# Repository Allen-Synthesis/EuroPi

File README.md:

# EuroPi
The EuroPi is a user reprogrammable [Eurorack](https://en.wikipedia.org/wiki/Eurorack) module developed by [Allen Synthesis](https://allensynthesis.co.uk) that uses the [Raspberry Pi Pico](https://www.raspberrypi.com/products/raspberry-pi-pico/) to process and produce modular level signals based on code written in [MicroPython](https://micropython.org/). The entire project is open-source.

## Documentation
### Hardware
The hardware source files and documentation (including build guides) can be found in the [hardware overview](hardware/README.md), and kits can be bought directly from [Allen Synthesis](https://allensynthesis.square.site/product/europi-panel-pcb/16?cp=true&sa=true&sbp=false&q=false).

### Software
Before using any of the software, follow the [programming_instructions](software/programming_instructions.md) to set up and calibrate your module.
A list of user contributed scripts (along with descriptions for their usage) can be found in [contrib/README.md](software/contrib/README.md).

The EuroPi firmware allows you to interact with the hardware easily using code written in MicroPython. You can read the full list of available functions in the [EuroPi API Documentation](https://allen-synthesis.github.io/EuroPi/), which also includes some examples of some of those functions can be used. Some of the less obvious but potentially useful functions are also explained in more depth in [interesting_things.md](software/interesting_things.md).

If you would like to extend any of the features of the EuroPi software, you can view the [firmware source code](software/firmware/europi.py), and make contributions of your own after reading the [contribution guidelines](contributing.md).

### Issues
If you find any bugs, either in the software, the hardware, or the documentation, please [create a GitHub issue](https://github.com/Allen-Synthesis/EuroPi/issues/new/choose) so it can be fixed by one of the maintainers. There are issue templates available, so please choose whichever is most relevant.

### AI Policy 
This is a project that is both explicitly aware of, and reliant on, its social context; the module's licenses are deliberately 'free' and open-source, and that fact is what has allowed its community to develop itself, and consequently develop the EuroPi module.
To paraphrase [Dan McQuillan](https://www.youtube.com/watch?v=mh0U2o5Ysms), "AI removes the cultural context that underpins our social relations" - A tool which produces an output without regard for social context cannot be used to meaningfully contribute to any project that specifically aims to analyse and engage with that context.

We are not able to know with certainty that any contribution is AI-free, however any pull requests which have clearly relied on it will be rejected. For the reasons described above we hope that you will choose to develop without it, not just to ensure a quick merge, but for the benefit of the open-source community and society as a whole.
All of the core components of the EuroPi (the firmware and hardware) are entirely AI-free.

## Specification
* 6 0-10V Control Voltage outputs, each with indicator LED
* 2 Knobs with 12 bit resolution
* 2 Push Buttons
* 1 0-12V Control Voltage input with 12 bit resolution
* 1 Digital input for external clocking or gate sources
* 128x32 OLED Display
* I²C expansion header on the rear for extra sensors or outputs

## License
This module, and any documentation included in this repository, is entirely "free" software and hardware. The hardware is [certified by the Open Source Hardware Association](https://certification.oshwa.org/uk000048.html)

* Software: [Apache 2.0](software/LICENSE)
* Hardware: [CERN OHL-S v2](hardware/LICENSE)
* Documentation: [CC0 1.0](LICENSE)

Anyone is welcome to design their own versions of the idea, or modify my designs.
The only thing I would ask is that you refrain from using the brand name 'Allen Synthesis' on your DIY builds if they have modified my files in any way, just to prevent any confusion if they end up being re-sold or distributed. This is in line with section 8.2 of the CERN license. You may use the brand name if you have simply copied the files from this repository to replicate without modification.

If you have a bug fix or improvement that you think is worth sharing, then feel free to send over any pictures or documentation and it can be merged with the main project!

## Disclaimer
Recreate any of the files found in this repository at your own risk; I will attempt to solve any issues that you might have with my designs, but I can't guarantee that there are not minor bugs in any of the documents, both hardware and software. If you want a module or kit that you know will work and will have customer support, you can order one directly from [Allen Synthesis](https://allensynthesis.co.uk/).

**NOTE:** This repository relates to the EuroPi module, however some users may be expecting to see what is now referred to as the 'EuroPi Prototype'. The repository for this (now deprecated) module [can be found here](https://github.com/roryjamesallen/EuroPi-Prototype)

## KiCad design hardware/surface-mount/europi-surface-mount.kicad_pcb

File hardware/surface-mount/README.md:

# EuroPi (surface-mount)

This is a version of the EuroPi that has all of the components other than the Pico, power header, and panel components pre-soldered using SMD packages. This makes for a much simpler DIY build, as well as a thinner end result. It has identical technical specifications to the through-hole version and adds the hardware required for input detection.

The board files for this version are designed in [KiCad](https://www.kicad.org/) so are a more friendly starting point for third-party development or modification.

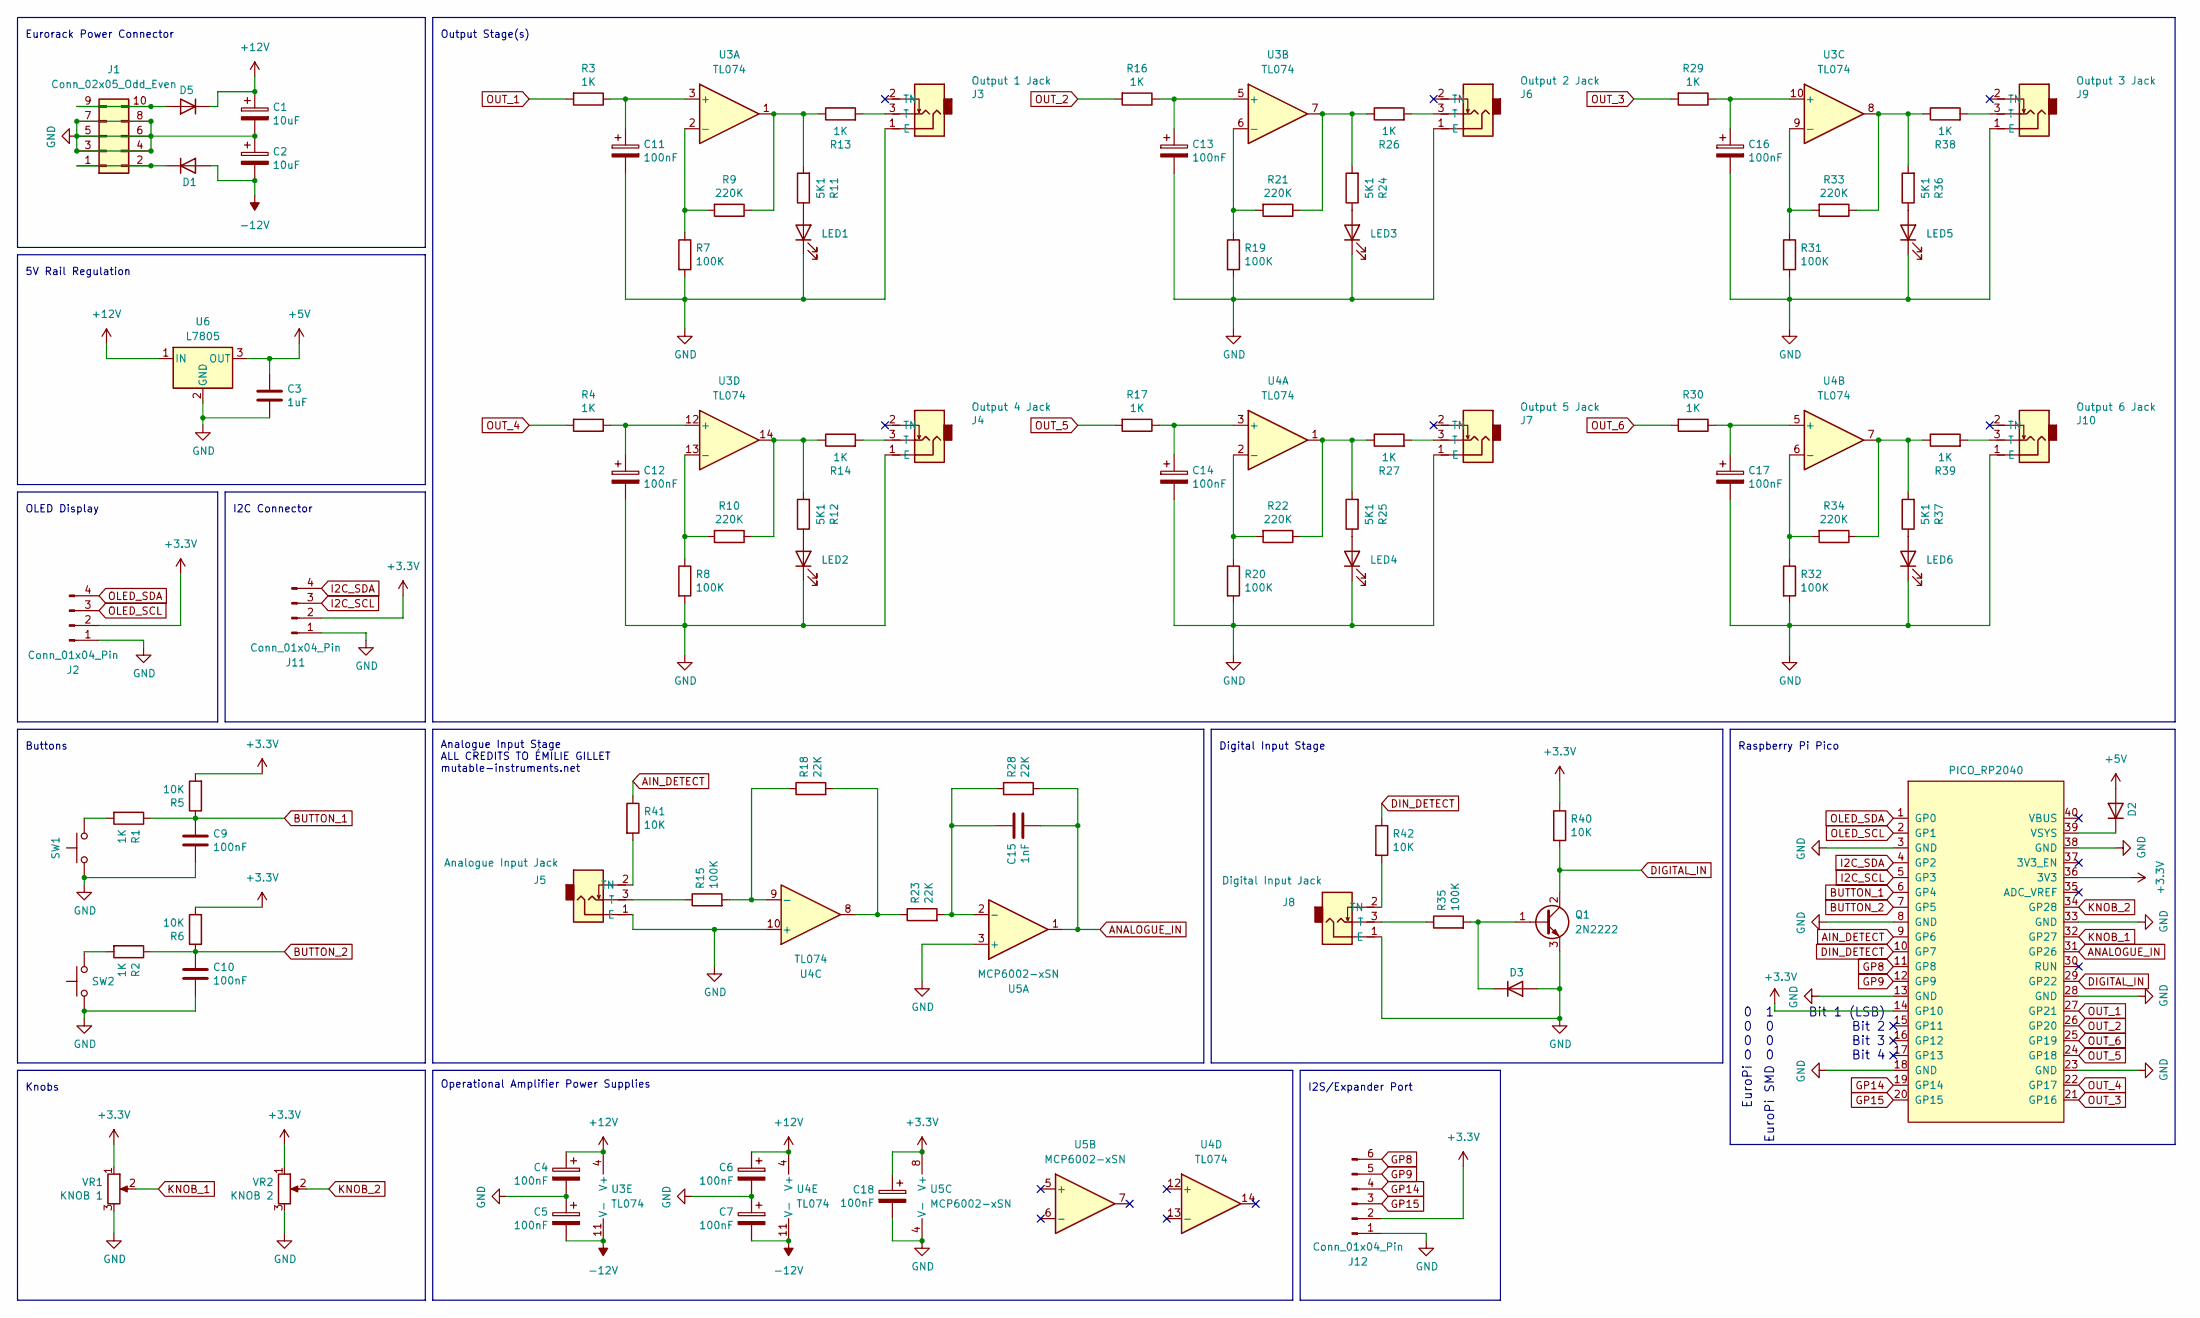
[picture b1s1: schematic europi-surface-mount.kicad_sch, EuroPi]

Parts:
C1, C2: 10uF; C_0805_2012Metric
C3: 1uF; C_0603_1608Metric
C4, C5, C6, C7, C9, C10, C11, C12, C13, C14, C16, C17, C18: 100nF; C_0603_1608Metric
C15: 1nF; C_0603_1608Metric
D1, D2, D5: D; D_SMA; LCSC Part C5356810
D3: D; D_SMA; LCSC Part C5148475
J1: Conn_02x05_Odd_Even; power-header-10-pin-unlabelled
J2: Conn_01x04_Pin; PinHeader_1x04_P2.54mm_Vertical
J3: Output 1 Jack; jack-thonkiconn-mono
J4: Output 4 Jack; jack-thonkiconn-mono
J5: Analogue Input Jack; jack-thonkiconn-mono
J6: Output 2 Jack; jack-thonkiconn-mono
J7: Output 5 Jack; jack-thonkiconn-mono
J8: Digital Input Jack; jack-thonkiconn-mono
J9: Output 3 Jack; jack-thonkiconn-mono
J10: Output 6 Jack; jack-thonkiconn-mono
J11: Conn_01x04_Pin; JST_PH_B4B-PH-K_1x04_P2.00mm_Vertical
J12: Conn_01x04_Pin; JST_PH_B6B-PH-K_1x06_P2.00mm_Vertical
LED1, LED2, LED3, LED4, LED5, LED6: LED; led-3mm
Q1: 2N2222; SOT-89-3; LCSC Part C21714170
R1, R2, R3, R4, R13, R14, R16, R17, R26, R27, R29, R30, R38, R39: 1K; R_0603_1608Metric
R5, R6, R40, R41, R42: 10K; R_0603_1608Metric
R7, R8, R15, R19, R20, R31, R32, R35: 100K; R_0603_1608Metric
R9, R10, R21, R22, R33, R34: 220K; R_0603_1608Metric
R11, R12, R24, R25, R36, R37: 5K1; R_0603_1608Metric
R18, R23, R28: 22K; R_0603_1608Metric
SW1, SW2: SW_Push; switch-momentary-c&k
U2: PICO_RP2040; raspberry-pi-pico
U3, U4: TL074; SOIC-14_3.9x8.7mm_P1.27mm; LCSC Part C6963
U5: MCP6002-xSN; SOIC-8_3.9x4.9mm_P1.27mm; LCSC Part C7377
U6: L7805; TO-252-2; LCSC Part C7394043
VR1: KNOB 1; potentiometer-9mm
VR2: KNOB 2; potentiometer-9mm

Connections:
+3.3V: C18.1, J2.2, J11.2, J12.2, R5.2, R6.2, R40.1, U2.14 (GP10), U2.36 (3V3), U5.8 (V+), VR1.1, VR2.1
+5V: C3.1, D2.2 (A), U6.3 (OUT)
+12V: C1.1, C4.1, C6.1, D5.1 (K), U3.4 (V+), U4.4 (V+), U6.1 (IN)
-12V: C2.2, C5.2, C7.2, D1.2 (A), U3.11 (V-), U4.11 (V-)
AIN_DETECT: R41.1, U2.9 (GP6)
ANALOGUE_IN: C15.2, R28.2, U2.31 (GP26), U5.1
BUTTON_1: C9.1, R1.1, R5.1, U2.6 (GP4)
BUTTON_2: C10.1, R2.1, R6.1, U2.7 (GP5)
DIGITAL_IN: Q1.2 (C), R40.2, U2.29 (GP22)
DIN_DETECT: R42.1, U2.10 (GP7)
GND: C1.2, C2.1, C3.2, C4.2, C5.1, C6.2, C7.1, C9.2, C10.2, C11.2, C12.2, C13.2, C14.2, C16.2, C17.2, C18.2, D3.2 (A), J1.3, J1.4, J1.5, J1.6, J1.7, J1.8, J2.1, J3.1 (E), J4.1 (E), J5.1 (E), J6.1 (E), J7.1 (E), J8.1 (E), J9.1 (E), J10.1 (E), J11.1, J12.1, LED1.1 (K), LED2.1 (K), LED3.1 (K), LED4.1 (K), LED5.1 (K), LED6.1 (K), Q1.3 (E), R7.2, R8.2, R19.2, R20.2, R31.2, R32.2, SW1.1, SW2.1, U2.3 (GND), U2.8 (GND), U2.13 (GND), U2.18 (GND), U2.23 (GND), U2.28 (GND), U2.33 (GND), U2.38 (GND), U4.10 (+), U5.3 (+), U5.4 (V-), U6.2 (GND), VR1.3, VR2.3
GP8: J12.6, U2.11 (GP8)
GP9: J12.5, U2.12 (GP9)
GP14: J12.4, U2.19 (GP14)
GP15: J12.3, U2.20 (GP15)
I2C_SCL: J11.3, U2.5 (GP3)
I2C_SDA: J11.4, U2.4 (GP2)
KNOB_1: U2.32 (GP27), VR1.2
KNOB_2: U2.34 (GP28), VR2.2
unnamed: D1.1 (K), J1.1, J1.2
unnamed: D2.1 (K), U2.39 (VSYS)
unnamed: D3.1 (K), Q1.1 (B), R35.2
unnamed: D5.2 (A), J1.9, J1.10
unnamed: J3.3 (T), R13.2
unnamed: J4.3 (T), R14.2
unnamed: J5.3 (T), R15.1
unnamed: J5.2 (TN), R41.2
unnamed: J6.3 (T), R26.2
unnamed: J7.3 (T), R27.2
unnamed: J8.3 (T), R35.1
unnamed: J8.2 (TN), R42.2
unnamed: J9.3 (T), R38.2
unnamed: J10.3 (T), R39.2
unnamed: LED1.2 (A), R11.1
unnamed: LED2.2 (A), R12.1
unnamed: LED3.2 (A), R24.1
unnamed: LED4.2 (A), R25.1
unnamed: LED5.2 (A), R36.1
unnamed: LED6.2 (A), R37.1
unnamed: R1.2, SW1.2
unnamed: R2.2, SW2.2
unnamed: R10.1, R12.2, R14.1, U3.14
unnamed: R9.1, R11.2, R13.1, U3.1
unnamed: R18.2, R23.1, U4.8
unnamed: R21.1, R24.2, R26.1, U3.7
unnamed: R22.1, R25.2, R27.1, U4.1
unnamed: R33.1, R36.2, R38.1, U3.8
unnamed: R34.1, R37.2, R39.1, U4.7
unnamed: C11.1, R3.1, U3.3 (+)
unnamed: R7.1, R9.2, U3.2 (-)
unnamed: C13.1, R16.1, U3.5 (+)
unnamed: R19.1, R21.2, U3.6 (-)
unnamed: C16.1, R29.1, U3.10 (+)
unnamed: R31.1, R33.2, U3.9 (-)
unnamed: C12.1, R4.1, U3.12 (+)
unnamed: R8.1, R10.2, U3.13 (-)
unnamed: C14.1, R17.1, U4.3 (+)
unnamed: R20.1, R22.2, U4.2 (-)
unnamed: C17.1, R30.1, U4.5 (+)
unnamed: R32.1, R34.2, U4.6 (-)
unnamed: R15.2, R18.1, U4.9 (-)
unnamed: C15.1, R23.2, R28.1, U5.2 (-)
OLED_SCL: J2.3, U2.2 (GP1)
OLED_SDA: J2.4, U2.1 (GP0)
OUT_1: R3.2, U2.27 (GP21)
OUT_2: R16.2, U2.26 (GP20)
OUT_3: R29.2, U2.21 (GP16)
OUT_4: R4.2, U2.22 (GP17)
OUT_5: R17.2, U2.24 (GP18)
OUT_6: R30.2, U2.25 (GP19)

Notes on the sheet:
Eurorack Power Connector
I2S/Expander Port
0 1 0 0 0 0 0 0
Operational Amplifier Power Supplies
Raspberry Pi Pico
Digital Input Stage
EuroPi SMD
5V Rail Regulation
Output Stage(s)
I2C Connector
Buttons
EuroPi
OLED Display
Analogue Input Stage ALL CREDITS TO ÉMILIE GILLET mutable-instruments.net
Knobs
Bit 1 (LSB) Bit 2 Bit 3 Bit 4

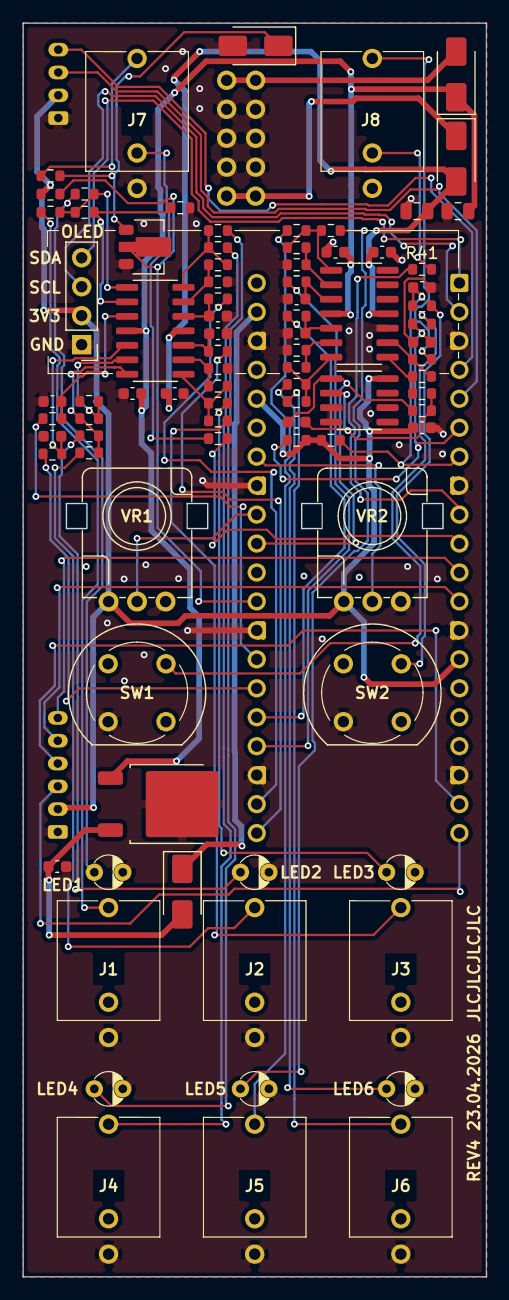
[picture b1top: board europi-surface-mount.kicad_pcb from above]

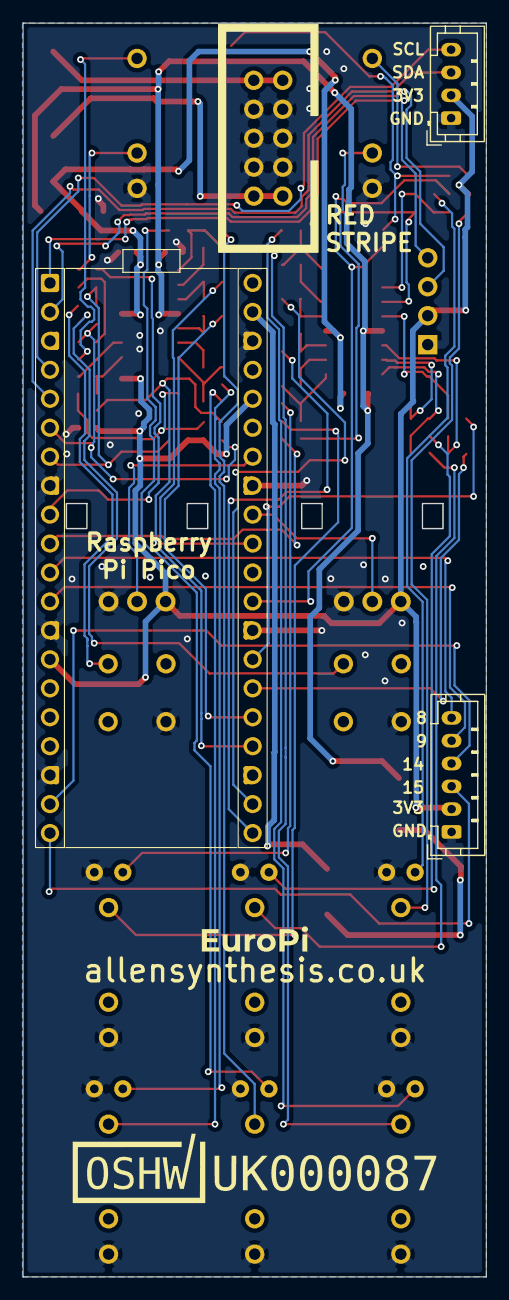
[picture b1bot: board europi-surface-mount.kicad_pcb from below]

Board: 2 copper layers, 40.6 x 110.0 mm, 91 parts (4 on the bottom side), 70 nets.

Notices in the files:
hardware/EuroPi/kicad/EuroPi.kicad_sch:
CC BY-SA 3.0
